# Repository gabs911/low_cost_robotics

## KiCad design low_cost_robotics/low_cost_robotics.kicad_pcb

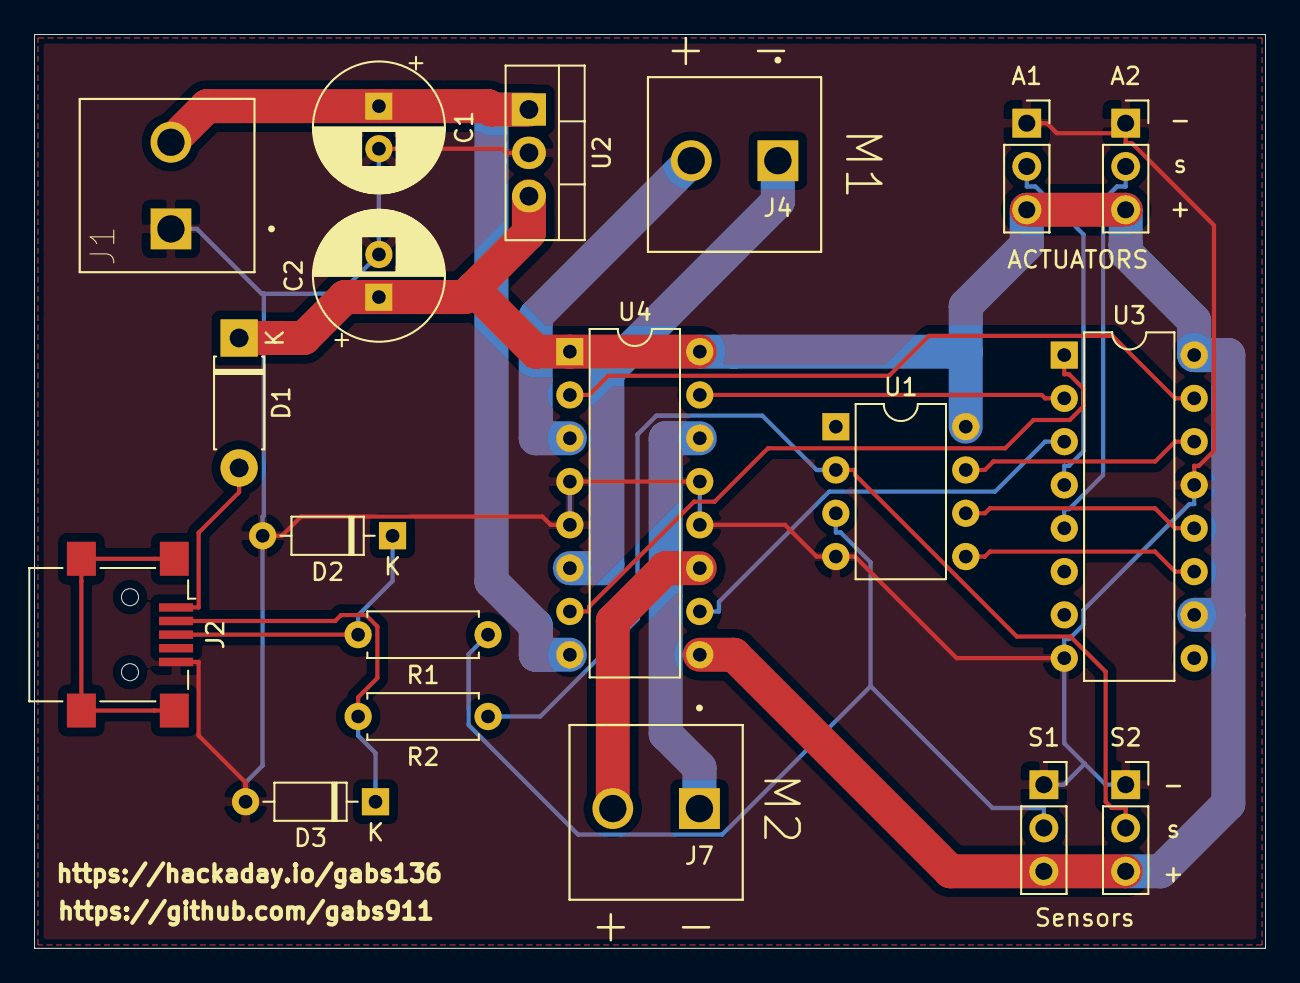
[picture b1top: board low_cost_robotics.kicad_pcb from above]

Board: 2 copper layers, 72.2 x 53.6 mm, 19 parts (0 on the bottom side), 21 nets.

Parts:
A1, A2: Conn_01x03_Female; PinSocket_1x03_P2.54mm_Vertical
C1: 100uF; CP_Radial_D7.5mm_P2.50mm
C2: 10uF; CP_Radial_D7.5mm_P2.50mm
D1: 1N5819; D_DO-41_SOD81_P7.62mm_Horizontal
D2, D3: D_Zener; D_DO-35_SOD27_P7.62mm_Horizontal
J1: Screw_Terminal_01x02; CUI_TB007-508-02BE
J2: USB_B_Mini; USB_Mini-B_Lumberg_2486_01_Horizontal
J4, J7: Conn_01x02_Female; CUI_TB007-508-02BE
R1, R2: 66.5; R_Axial_DIN0207_L6.3mm_D2.5mm_P7.62mm_Horizontal
S1, S2: Conn_01x03_Female; PinSocket_1x03_P2.54mm_Vertical
U1: ATtiny85-20PU; DIP-8_W7.62mm
U2: L7805; TO-220-3_Vertical
U3: 74HC595; DIP-16_W7.62mm
U4: L293D; DIP-16_W7.62mm

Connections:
5V: A1.3, A2.3, C2.1, D1.1, S1.3, S2.3, U1.8, U2.3, U3.10, U3.16, U4.1, U4.9, U4.16
D+: R1.1, S1.2, U1.3
D-: R2.1, S2.2, U1.2
GND: A1.1, A2.1, C1.2, C2.2, D2.2, D3.2, J1.1, J2.5, S1.1, S2.1, U1.4, U2.2, U3.8, U3.13, U4.4, U4.5, U4.12, U4.13
unnamed: D1.2, J2.1
unnamed: D2.1, J2.3, R1.2
unnamed: D3.1, J2.2, R2.2
OUT1: J4.2, U4.3
OUT2: J4.1, U4.6
OUT3: J7.2, U4.11
OUT4: J7.1, U4.14
PB0: U1.5, U3.11
PB1: U1.6, U3.12
PB2: U1.7, U3.14
QA: U3.15, U4.2
QB: U3.1, U4.7
QC: U3.2, U4.15
QD: U3.3, U4.10
QE: A1.2, U3.4
QF: A2.2, U3.5
V_Bat: C1.1, J1.2, U2.1, U4.8
